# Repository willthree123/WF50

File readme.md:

# WF50

WF50 is a 50-keys split keyboard.

Keyboard Maintainer: [willthree123](https://github.com/willthree123/) Instagram: [@kok.sc_jesse](https://instagram.com/kok.sc_jesse)  
Hardware Supported: ProMicro

Make example for this keyboard (after setting up your build environment):

    qmk compile -kb handwired/wf50 -km via

---

# WF50P

WF50P is a PCB version of WF50(50-keys split keyboard).

Keyboard Maintainer: [willthree123](https://github.com/willthree123/) Instagram: [@kok.sc_jesse](https://instagram.com/kok.sc_jesse)  
Hardware Supported: ProMicro

Make example for this keyboard (after setting up your build environment):

    qmk compile -kb wf50p -km via
---
See the [build environment setup](https://docs.qmk.fm/#/getting_started_build_tools) and the [make instructions](https://docs.qmk.fm/#/getting_started_make_guide) for more information. Brand new to QMK? Start with our [Complete Newbs Guide](https://docs.qmk.fm/#/newbs).

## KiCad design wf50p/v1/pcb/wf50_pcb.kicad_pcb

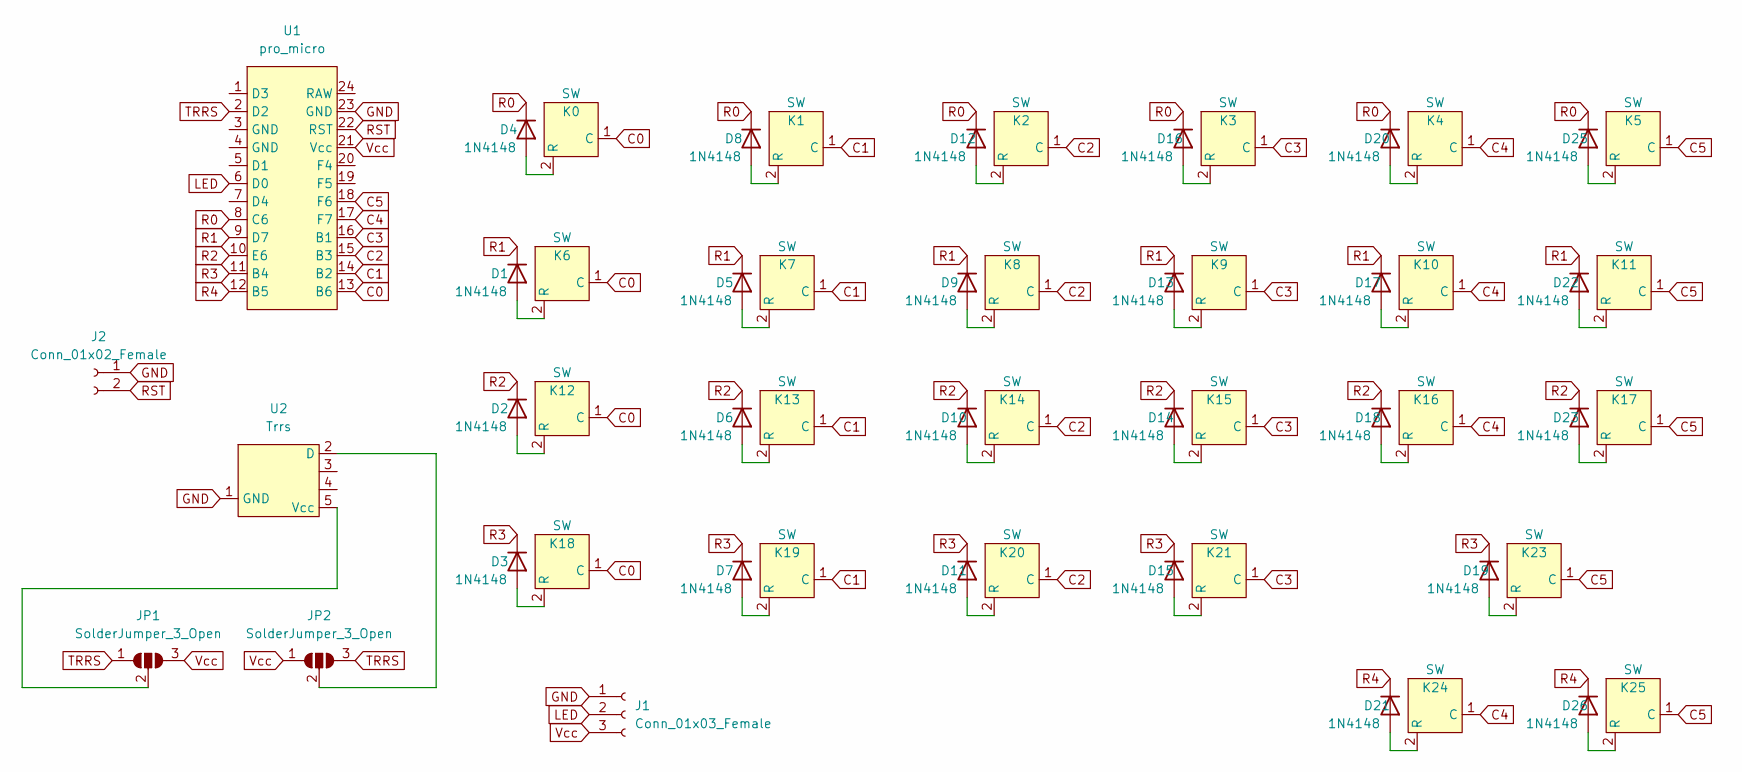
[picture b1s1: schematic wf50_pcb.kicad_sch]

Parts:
D1, D2, D3, D4, D5, D6, D7, D8, D9, D10, D11, D12, D13, D14, D15, D16, D17, D18, D19, D20, D21, D22, D23, D25, D26: 1N4148; D_DO-35_SOD27_P7.62mm_Horizontal
J1: Conn_01x03_Female; PinHeader_1x03_P2.54mm_Vertical
J2: Conn_01x02_Female; PinHeader_1x02_P2.00mm_Vertical
JP1, JP2: SolderJumper_3_Open; SolderJumper-3_P2.0mm_Open_TrianglePad1.0x1.5mm_NumberLabels
K0, K1, K2, K3, K4, K5, K6, K7, K8, K9, K10, K11, K12, K13, K14, K15, K16, K17, K18, K19, K20, K21, K23, K24, K25: SW; MXOnly-1U-user-split
U1: pro_micro; ProMicro-EnforcedTop
U2: Trrs; Trrs_user

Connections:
C0: K0.1 (C), K6.1 (C), K12.1 (C), K18.1 (C), U1.13 (B6)
C1: K1.1 (C), K7.1 (C), K13.1 (C), K19.1 (C), U1.14 (B2)
C2: K2.1 (C), K8.1 (C), K14.1 (C), K20.1 (C), U1.15 (B3)
C3: K3.1 (C), K9.1 (C), K15.1 (C), K21.1 (C), U1.16 (B1)
C4: K4.1 (C), K10.1 (C), K16.1 (C), K24.1 (C), U1.17 (F7)
C5: K5.1 (C), K11.1 (C), K17.1 (C), K23.1 (C), K25.1 (C), U1.18 (F6)
GND: J1.1, J2.1, U1.23 (GND), U2.1 (GND); also elsewhere on the board
LED: J1.2, U1.6 (D0); also elsewhere on the board
unnamed: D1.2 (A), K6.2 (R)
unnamed: D2.2 (A), K12.2 (R)
unnamed: D3.2 (A), K18.2 (R)
unnamed: D4.2 (A), K0.2 (R)
unnamed: D5.2 (A), K7.2 (R)
unnamed: D6.2 (A), K13.2 (R)
unnamed: D7.2 (A), K19.2 (R)
unnamed: D8.2 (A), K1.2 (R)
unnamed: D9.2 (A), K8.2 (R)
unnamed: D10.2 (A), K14.2 (R)
unnamed: D11.2 (A), K20.2 (R)
unnamed: D12.2 (A), K2.2 (R)
unnamed: D13.2 (A), K9.2 (R)
unnamed: D14.2 (A), K15.2 (R)
unnamed: D15.2 (A), K21.2 (R)
unnamed: D16.2 (A), K3.2 (R)
unnamed: D17.2 (A), K10.2 (R)
unnamed: D18.2 (A), K16.2 (R)
unnamed: D19.2 (A), K23.2 (R)
unnamed: D20.2 (A), K4.2 (R)
unnamed: D21.2 (A), K24.2 (R)
unnamed: D22.2 (A), K11.2 (R)
unnamed: D23.2 (A), K17.2 (R)
unnamed: D25.2 (A), K5.2 (R)
unnamed: D26.2 (A), K25.2 (R)
unnamed: JP1.2 (C), U2.5 (Vcc)
unnamed: JP2.2 (C), U2.2 (D)
R0: D4.1 (K), D8.1 (K), D12.1 (K), D16.1 (K), D20.1 (K), D25.1 (K), U1.8 (C6)
R1: D1.1 (K), D5.1 (K), D9.1 (K), D13.1 (K), D17.1 (K), D22.1 (K), U1.9 (D7)
R2: D2.1 (K), D6.1 (K), D10.1 (K), D14.1 (K), D18.1 (K), D23.1 (K), U1.10 (E6)
R3: D3.1 (K), D7.1 (K), D11.1 (K), D15.1 (K), D19.1 (K), U1.11 (B4)
R4: D21.1 (K), D26.1 (K), U1.12 (B5)
RST: J2.2, U1.22 (RST); also elsewhere on the board
TRRS: JP1.1 (A), JP2.3 (B), U1.2 (D2)
Vcc: J1.3, JP1.3 (B), JP2.1 (A), U1.21 (Vcc); also elsewhere on the board

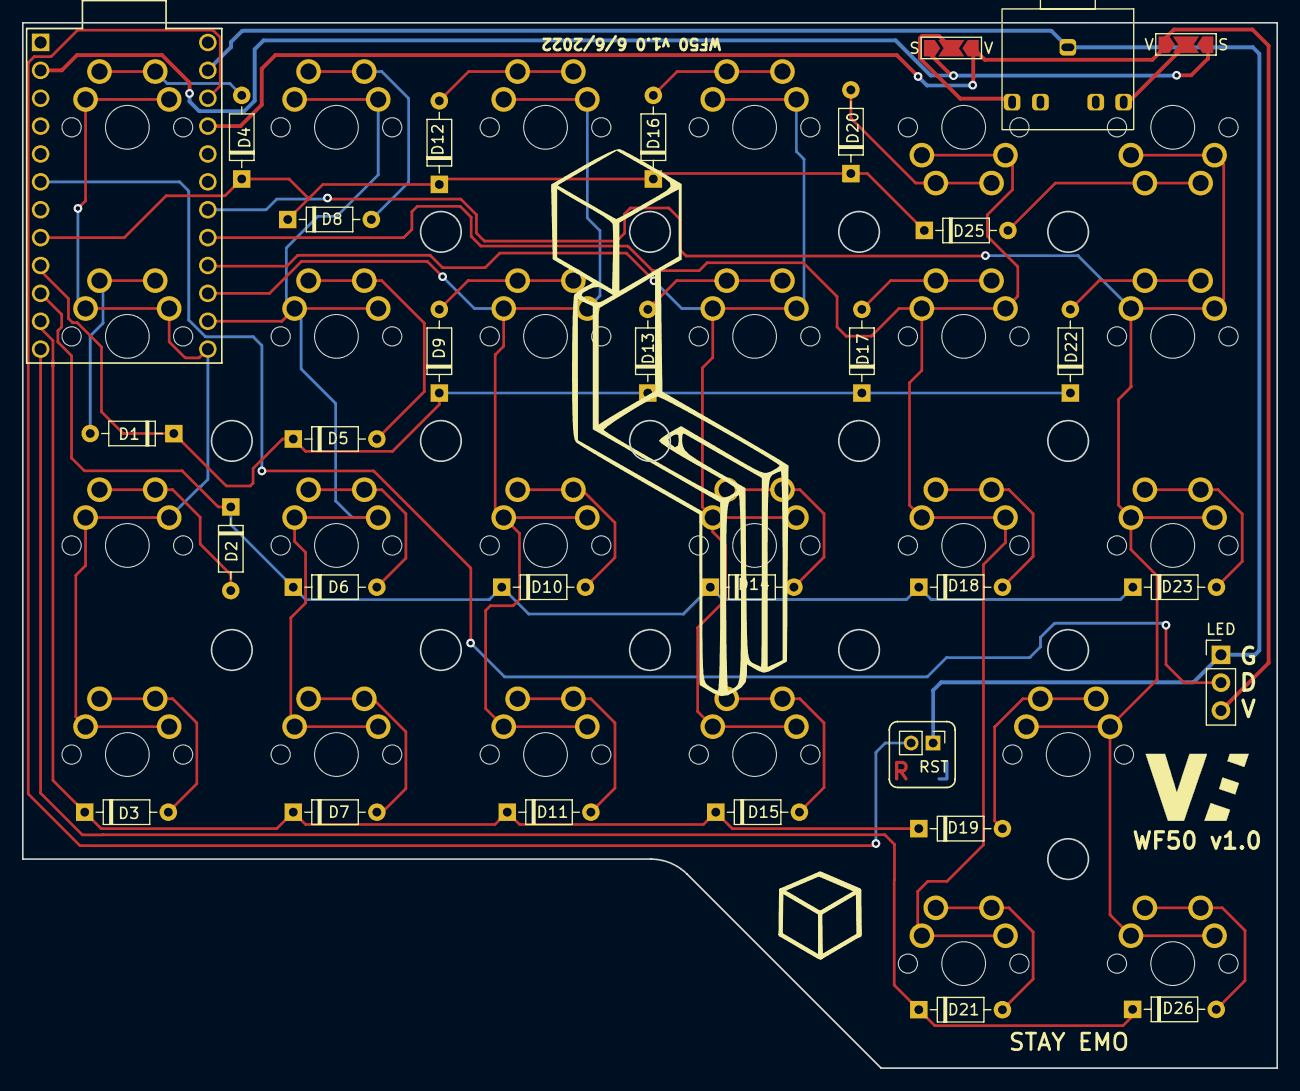
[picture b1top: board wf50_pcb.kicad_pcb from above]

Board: 2 copper layers, 114.3 x 95.2 mm, 56 parts (0 on the bottom side), 43 nets.

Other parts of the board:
LED: Conn_01x03_Female; PinHeader_1x03_P2.54mm_Vertical
RST: Conn_01x02_Female; PinHeader_1x02_P2.00mm_Vertical

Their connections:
GND: LED.1, RST.1; also elsewhere on the board
LED: LED.2; also elsewhere on the board
RST: RST.2; also elsewhere on the board
Vcc: LED.3; also elsewhere on the board

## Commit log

2021-05-31 1.2.0
2021-06-01 1.2.1
2021-10-30 Finsihed
2021-10-30 Final
2022-06-26 wf50p
